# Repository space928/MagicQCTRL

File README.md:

# MagicQCTRL
A custom controller for the MagicQ lighting software built around the Adafruit MacroPad RP2040.

## Building
The project is split into two parts, the software which runs on the macropad and the client application.

### Macropad Software
The software running on the MacroPad is a simple Arduino project which can be built using the PlatformIO extension for VSCode.

### Client Application
The client application is written in .NET 7 and can be built with any modern version of Visual Studio with support for .NET 7.

## Data Flow

```

  ==================       USB HID Messages    [________________ - [] X ]                          [_______________ - [] X ]
  | O  #####  O  O |   ----- Key Press ----->  [                        ]  ---- OSC Message ---->  [ MagicQ                ]
  | O  [] [] []  O |   ---- Button Press --->  [                        ]                          [                       ]
  | O  [] [] []  O |   ---- Encoder Move --->  [                        ]  ---- Memory Read ---->  [                       ]
  | O  [] [] []  O |                           [                        ]  <--- Memory Write ----  [                       ]
  |    [] [] []    |   <-- Update Profile ---  [                        ]                          [                       ]
  |                |                           [                        ]                          [                       ]
  ==================                           [________________________]                          [                       ]
  MagicQ CTRL Hardware                         Client app                                          MagicQ

```

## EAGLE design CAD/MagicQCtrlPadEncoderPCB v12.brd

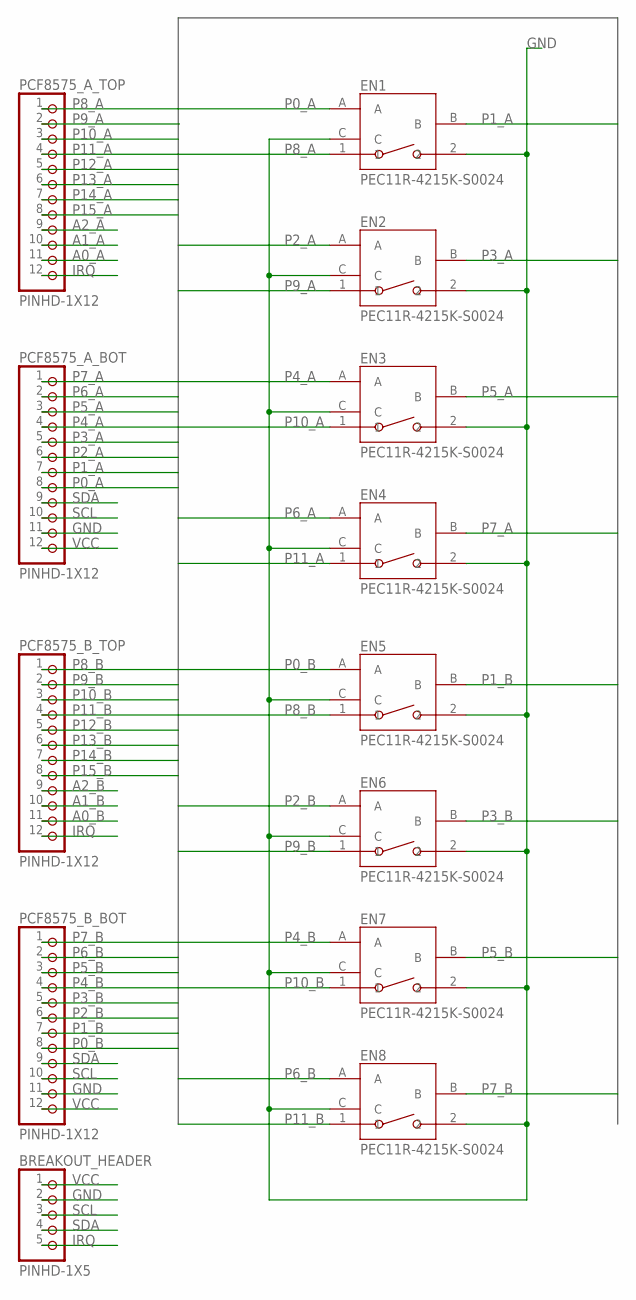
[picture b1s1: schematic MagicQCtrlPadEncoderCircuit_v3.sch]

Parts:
BREAKOUT_HEADER: PINHD-1X5; 1X05
EN1, EN2, EN3, EN4, EN5, EN6, EN7, EN8: PEC11R-4215K-S0024
PCF8575_A_BOT, PCF8575_A_TOP, PCF8575_B_BOT, PCF8575_B_TOP: PINHD-1X12; 1X12

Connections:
A0_A: PCF8575_A_TOP.11
A0_B: PCF8575_B_TOP.11
A1_A: PCF8575_A_TOP.10
A1_B: PCF8575_B_TOP.10
A2_A: PCF8575_A_TOP.9
A2_B: PCF8575_B_TOP.9
GND: BREAKOUT_HEADER.2, EN1.2, EN1.C, EN2.2, EN2.C, EN3.2, EN3.C, EN4.2, EN4.C, EN5.2, EN5.C, EN6.2, EN6.C, EN7.2, EN7.C, EN8.2, EN8.C, PCF8575_A_BOT.11, PCF8575_B_BOT.11
IRQ: BREAKOUT_HEADER.5, PCF8575_A_TOP.12, PCF8575_B_TOP.12
P0_A: EN1.A, PCF8575_A_BOT.8
P0_B: EN5.A, PCF8575_B_BOT.8
P1_A: EN1.B, PCF8575_A_BOT.7
P1_B: EN5.B, PCF8575_B_BOT.7
P2_A: EN2.A, PCF8575_A_BOT.6
P2_B: EN6.A, PCF8575_B_BOT.6
P3_A: EN2.B, PCF8575_A_BOT.5
P3_B: EN6.B, PCF8575_B_BOT.5
P4_A: EN3.A, PCF8575_A_BOT.4
P4_B: EN7.A, PCF8575_B_BOT.4
P5_A: EN3.B, PCF8575_A_BOT.3
P5_B: EN7.B, PCF8575_B_BOT.3
P6_A: EN4.A, PCF8575_A_BOT.2
P6_B: EN8.A, PCF8575_B_BOT.2
P7_A: EN4.B, PCF8575_A_BOT.1
P7_B: EN8.B, PCF8575_B_BOT.1
P8_A: EN1.1, PCF8575_A_TOP.1
P8_B: EN5.1, PCF8575_B_TOP.1
P9_A: EN2.1, PCF8575_A_TOP.2
P9_B: EN6.1, PCF8575_B_TOP.2
P10_A: EN3.1, PCF8575_A_TOP.3
P10_B: EN7.1, PCF8575_B_TOP.3
P11_A: EN4.1, PCF8575_A_TOP.4
P11_B: EN8.1, PCF8575_B_TOP.4
P12_A: PCF8575_A_TOP.5
P12_B: PCF8575_B_TOP.5
P13_A: PCF8575_A_TOP.6
P13_B: PCF8575_B_TOP.6
P14_A: PCF8575_A_TOP.7
P14_B: PCF8575_B_TOP.7
P15_A: PCF8575_A_TOP.8
P15_B: PCF8575_B_TOP.8
SCL: BREAKOUT_HEADER.3, PCF8575_A_BOT.10, PCF8575_B_BOT.10
SDA: BREAKOUT_HEADER.4, PCF8575_A_BOT.9, PCF8575_B_BOT.9
VCC: BREAKOUT_HEADER.1, PCF8575_A_BOT.12, PCF8575_B_BOT.12

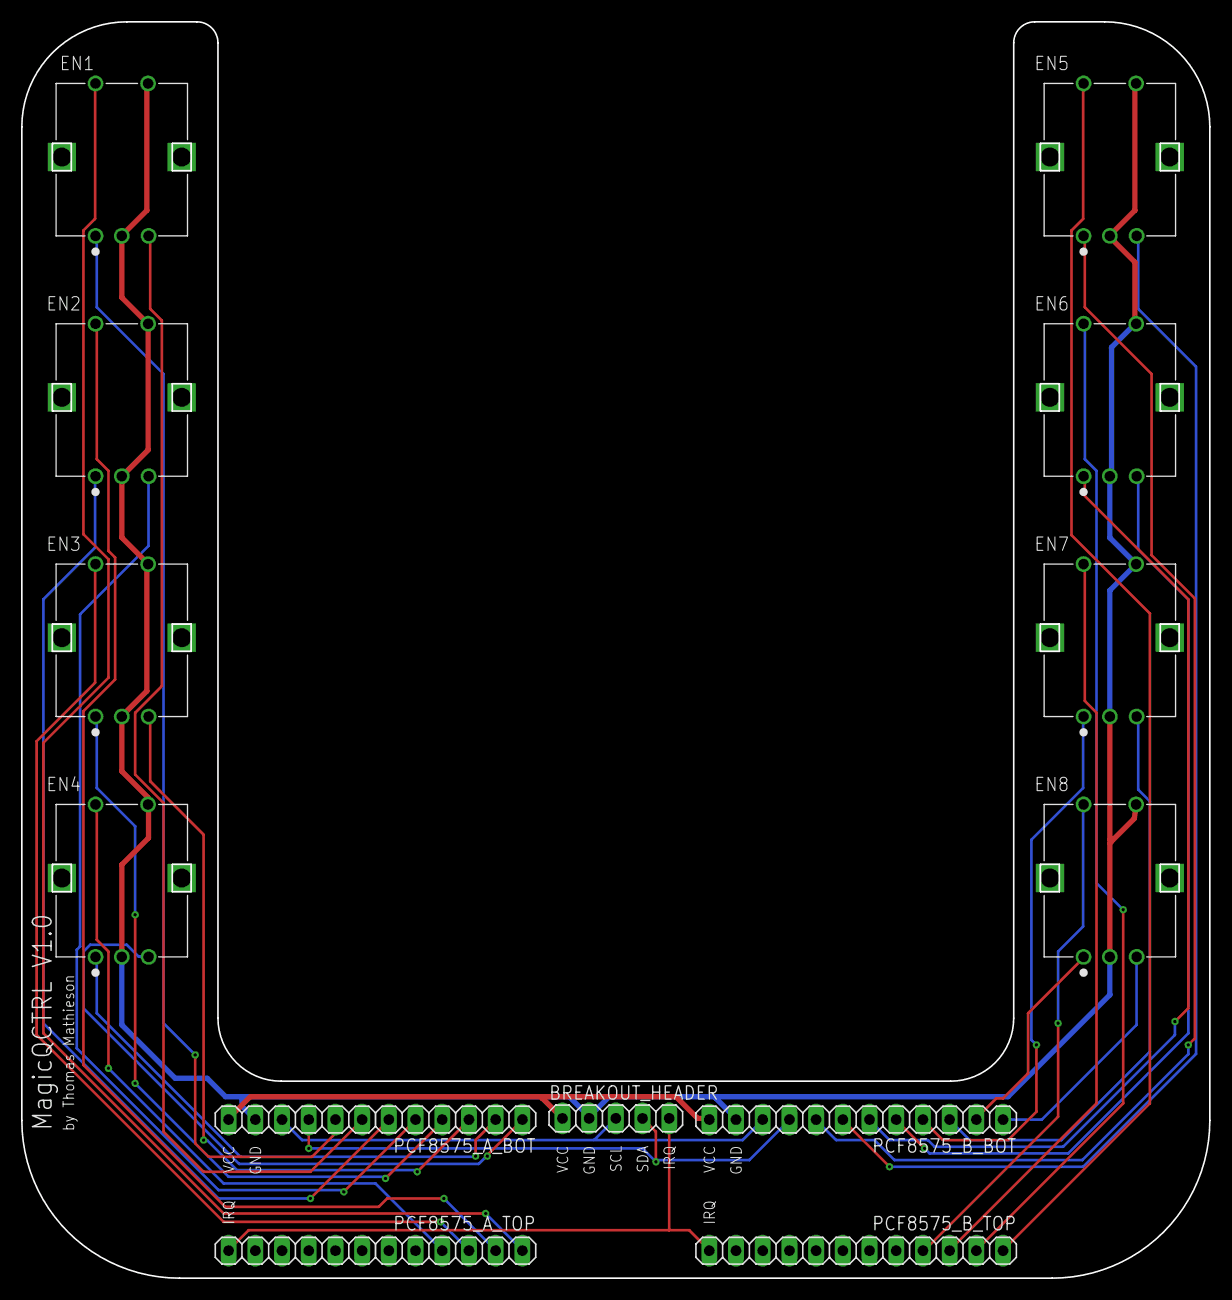
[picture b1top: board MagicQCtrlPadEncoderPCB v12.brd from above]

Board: 2 copper layers, 113.0 x 119.5 mm, 13 parts (0 on the bottom side), 29 nets.

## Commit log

2023-01-09 Initital commit
2023-02-15 Refactoring and new c# project: - Added gitignore - Moved arduino modules to src/modules - Added c# project
2023-02-15 Create LICENSE
2023-03-23 Improved C# UI + Added PIO Config
2023-05-09 General progress on all fronts: - Added python utility for debugging USB HID messages - Added proposed key layout - Added debugging/logging library to the Arduino project - Added icon - Updated C# as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
2023-05-10 Many improvements and new functionality: - Implemented button editor - Added OSC support - Added key rgb backlight control - Added key names to the OLED - Implemented USB configuration messages - Fix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
2023-05-12 Started implemented MagicQ interoperability: - Project now requires 32-bit compilation for remote method calls to work, currently required for special functions - Added UI for special functions - Add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
2023-05-13 Interoperability with MagicQ: - Added grouping to the items in the SpecialFunctions dropdown - Added support for setting a custom MagicQ keycode (mostly for debugging) - Added loads of new MagicQ key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
2023-05-17 Progress on encoders + Some Tidying: - Added a safety check for invalid specialFunction values from json files - Added EncoderType enum - Rewrote the MagicQDriver class to make it more robust - Added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
2023-07-13 - Added updated CAD files - Added optional PCB CAD files - Added encoder support to C# app (Encoder emulation for MagicQ) - Added dark theme to colour picker - Improved UI - FIxed a few bugs - Added 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
2023-08-29 Implemented support for Execute items: - Added UI for triggering execute items - Implemented data model for execute items - Implemented hooks for execute items - Implemented special OpenLayout, Reset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
2024-02-15 Version 1.5: - Added splash screen - Fixed crash with Layout buttons - Fixed execute items - Updated copyright Arduino project: - Reduced encoder message rate and increased acceleration - Added setti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
2024-11-18 Support for displaying MagicQ key states: - Added support for reading the key light state of MagicQ keys - Small bugfixes - Updated .NET version - Updated dependencies - Refactoring
2024-11-26 OSC NIC selection and various bugfixes: - Enabled project-wide nulable - Refactored/reformated source code for consistency - Various changes to ensure explicit nullability compliance - Fixed connecti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
2025-02-04 Migrated to PlatformIO: - Migrated toolchain to PlatformIO - Updated platfomio ini - Moved C files into /src and /include - Implemented EtchASketch app - Implemented Snake app
2025-02-07 Added support for more MagicQ keys: - Added the remaining keys to the MagicQCTRLSpecialFunction enum - Added string formatter to pretty print the key names in the combobox
2026-02-27 Removed old dependencies added support for 64-bit MagicQ: - Removed Fody - Removed ReactiveUI - Replaced [Reative] properties with source generation - Added basic support for MagicQ 1.9.7.3 (this cur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
